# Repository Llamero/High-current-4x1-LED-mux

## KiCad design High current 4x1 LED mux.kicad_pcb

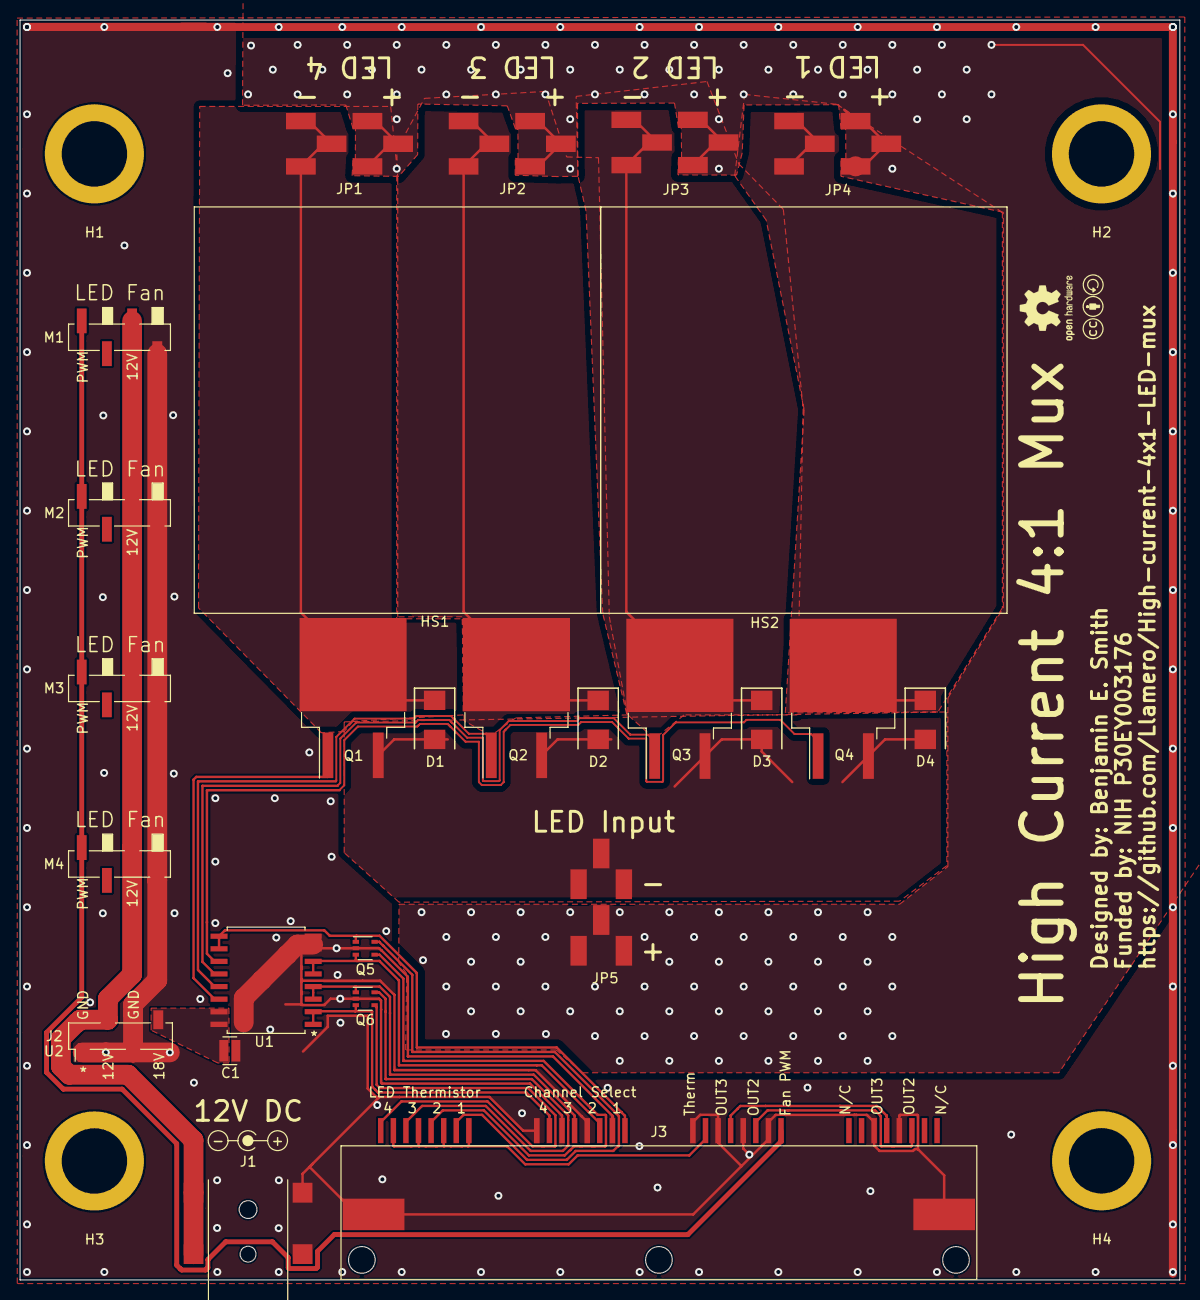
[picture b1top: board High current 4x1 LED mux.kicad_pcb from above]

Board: 2 copper layers, 117.0 x 127.1 mm, 34 parts (0 on the bottom side), 25 nets.

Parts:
C1: 2.2uF; 0508_Capacitor
D1, D2, D3, D4: TVS_Diode; DO-214AA
H1, H2, H3, H4: MountingHole; 14-20_standoff
HS1, HS2: HS-PCB; Heatsink_910-40-2-23-2-B-0
J1: Barrel_Jack_Switch; DC-jack_54-00165
J2: Conn_01x04_Female; DC_DC_converter-3S4A_1218S1UP
J3: 8P8C_Shielded_x4; RJ45_x4-RJSSE-5380-04
JP1, JP2, JP3, JP4, JP5: Quick Connect; 4928TR-power
LOGO1: CC license; Creative_commons_license
LOGO2: Jack Polarity; Polarity_Center_Positive
LOGO3: OSHW Logo; OSHW-Logo2_7.3x6mm_SilkScreen
M1, M2, M3, M4: Fan_4pin; 4-pin_fan_SMD
Q1, Q2, Q3, Q4: SUM70060E; TO-263-2
Q5, Q6: DMN32D2LDF-7; SOT-353_SC-70-5
U1: MIC4468ZWM-TR
U2: DC DC Converter; Ref_only

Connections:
/12V: J1.1, J2.2, M1.2, M2.2, M3.2, M4.2
/18V: C1.2, J2.4, U1.15, U1.16
/CH1: J3.17, Q5.1, U1.9, U1.10
/CH2: J3.19, Q5.3, U1.5, U1.6
/CH3: J3.21, Q6.1, U1.3, U1.4
/CH4: J3.23, Q6.3, U1.1, U1.2
/Fan_PWM: J3.9, M1.4, M2.4, M3.4, M4.4
/Gate1: Q4.1, U1.11
/Gate2: Q3.1, U1.12
/Gate3: Q2.1, U1.13
/Gate4: Q1.1, U1.14
/LED1-: D4.1, JP4.1, Q4.2
/LED2-: D3.1, JP3.1, Q3.2
/LED3-: D2.1, JP2.1, Q2.2
/LED4-: D1.1, JP1.1, Q1.2
/LED+: JP1.2, JP2.2, JP3.2, JP4.2, JP5.1
/LED-: D1.2, D2.2, D3.2, D4.2, JP5.2, Q1.3, Q2.3, Q3.3, Q4.3
/OUT2: J3.3, J3.11
/OUT3: J3.5, J3.13
/Therm1: J3.26, Q5.5
/Therm2: J3.28, Q5.4
/Therm3: J3.30, Q6.5
/Therm4: J3.32, Q6.4
/Thermistor: J3.15, J3.25, J3.27, J3.29, J3.31
GND: C1.1, J1.2, J1.3, J2.1, J2.3, J3.4, J3.6, J3.10, J3.12, J3.14, J3.16, J3.18, J3.20, J3.22, J3.24, J3.SH, M1.1, M2.1, M3.1, M4.1, Q5.2, Q6.2, U1.7, U1.8

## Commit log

2021-10-29 Preliminary layout
2021-11-05 Complete draft of PCB layout
2021-11-05 Have in and out numbering on driver match
2021-11-05 Add labels fix stand-off position
2021-11-06 Add Gerber files
2022-07-09 Bigger spacing on 100V planes to prevent shorting
